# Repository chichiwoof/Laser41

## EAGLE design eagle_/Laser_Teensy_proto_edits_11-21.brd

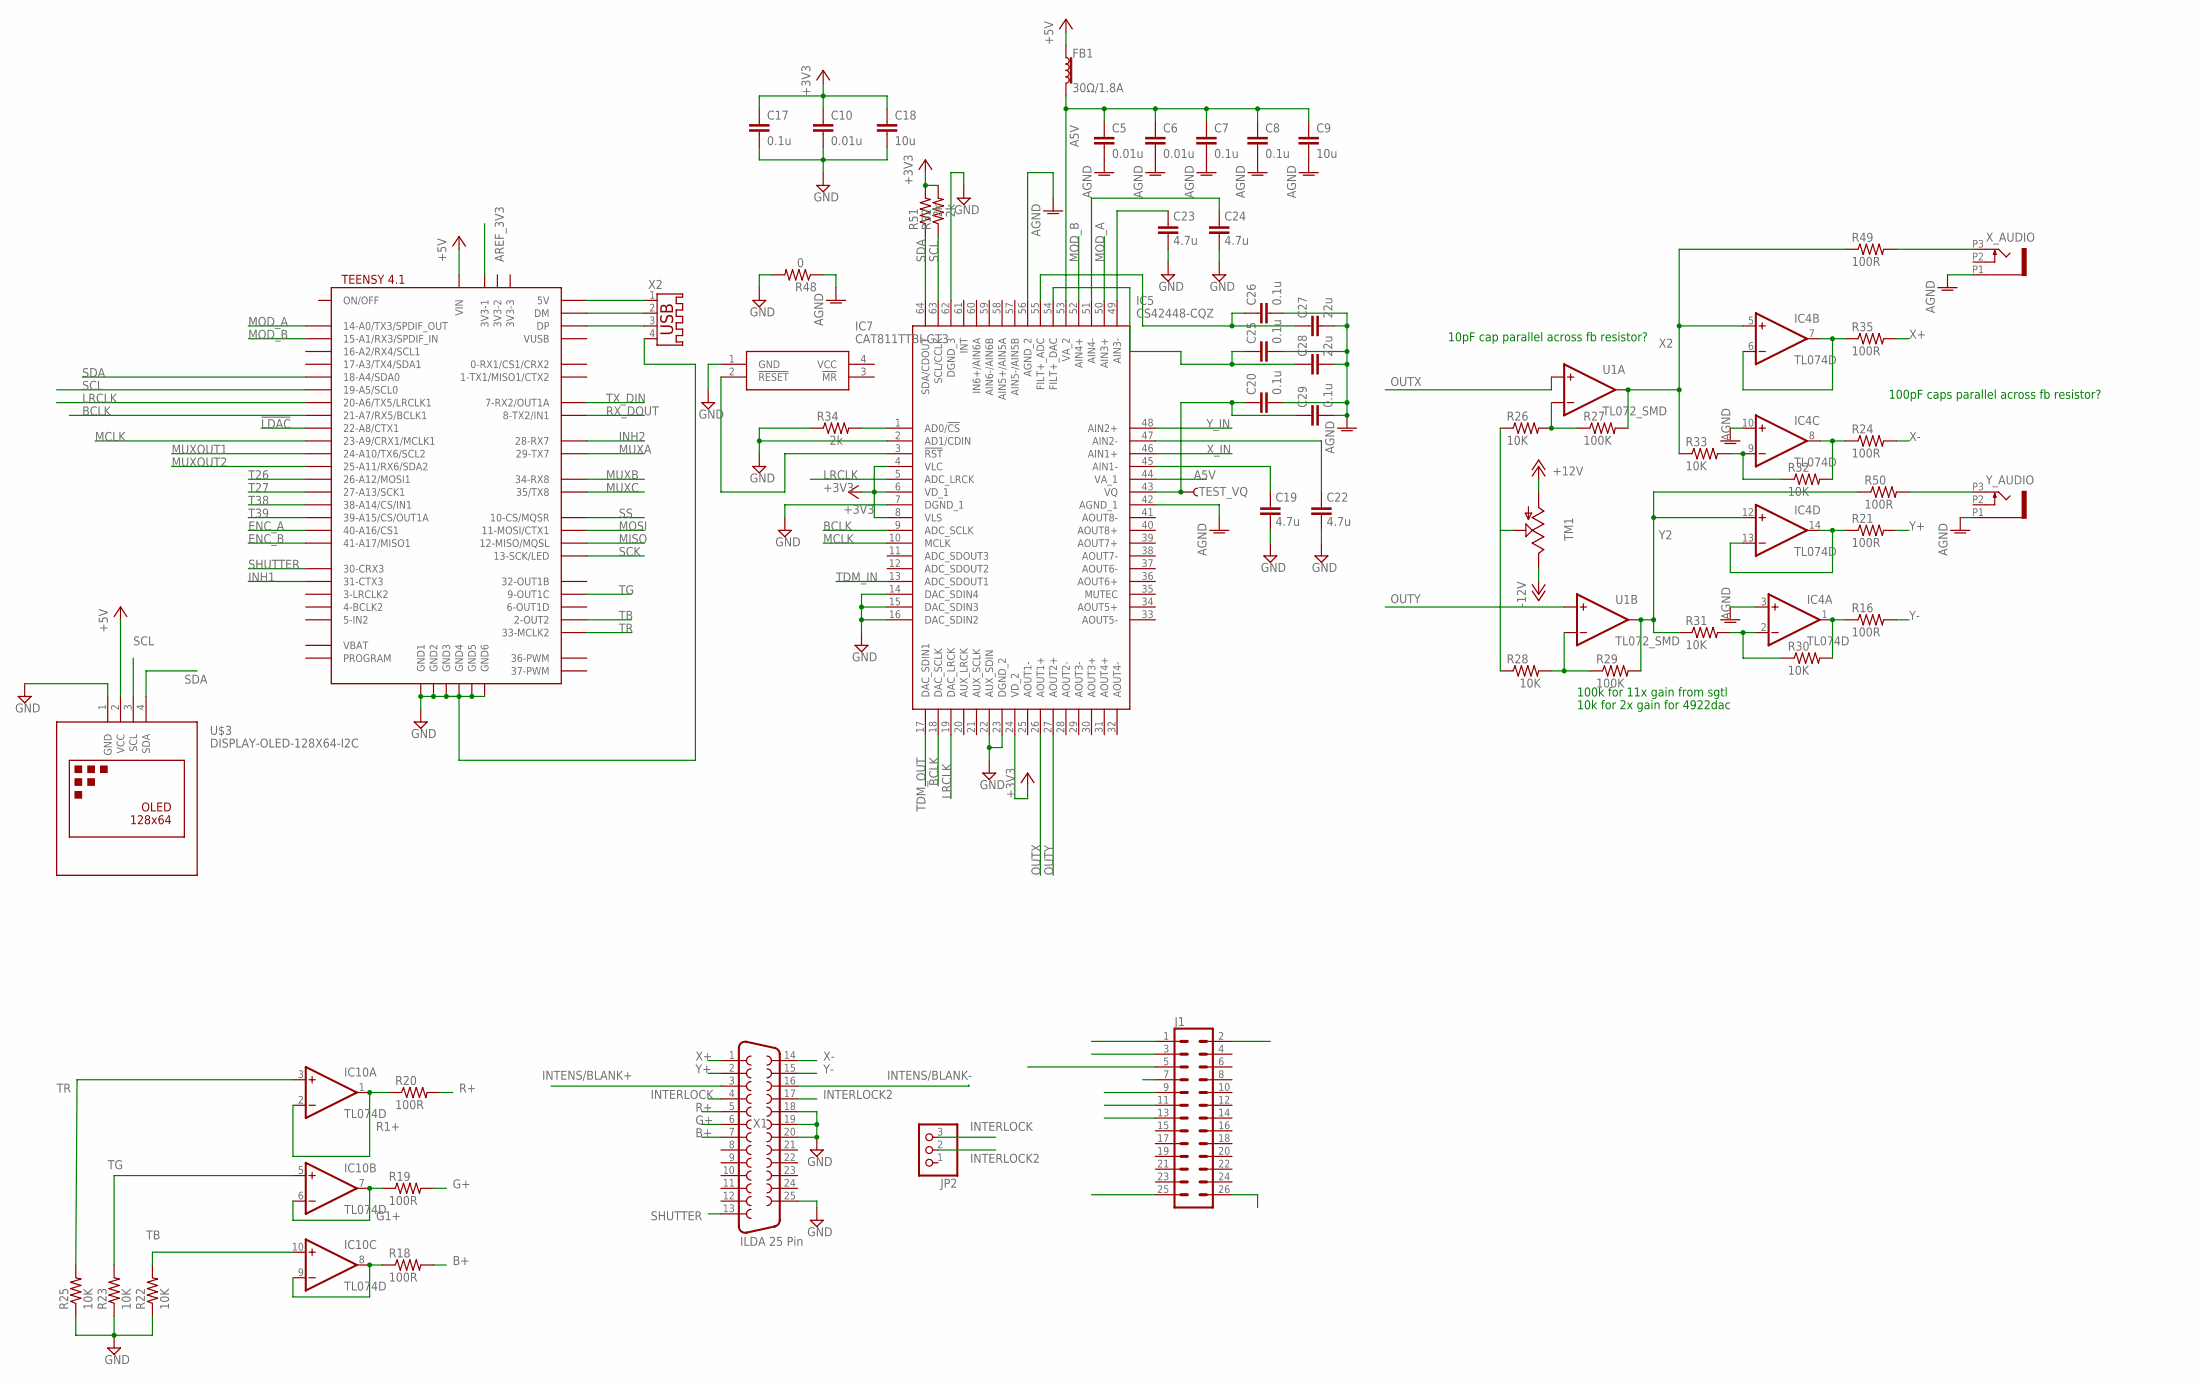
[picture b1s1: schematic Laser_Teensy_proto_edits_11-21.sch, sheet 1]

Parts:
C5, C6, C10: 0.01u; C0603
C7, C8, C17, C20, C25, C26, C29: 0.1u; C0603
C9, C18: 10u; C0603
C19, C22, C23, C24: 4.7u; C0603
C27, C28: 22u; C0603
FB1: 30Ω/1.8A; 0603
IC4, IC10: TL074D; SO14
IC5: CS42448-CQZ; QFP50P1200X1200X160-64N
IC7: CAT811TTBI-GT3; 4-PIN-SOT-143(BI-SUFFIX-CASE-5
J1: CONN_13X22X13; 2X13
JP2: PINHD-1X3; 1X03
R16, R18, R19, R20, R21, R24, R35, R49, R50: 100R; R0603
R22, R23, R25, R26, R28, R30, R31, R32, R33: 10K; R0603
R27, R29: 100K; R0603
R34, R51, R52: 2k; R0603
R48: 0; R0603
TEST_VQ: TEST-VQ; PAD.03X.03
TM1: TRIM; 6MM
U1: TL072_SMD; SO08
U$2: TEENSY41-E; TENNSY41-E
U$3: DISPLAY-OLED-128X64-I2C
X1: ILDA 25 Pin; F25D
X2: USB-A003
X_AUDIO: PJ301_THONKICONN6; WQP_PJ_301M6
Y_AUDIO: PJ301_THONKICONN6; WQP_PJ_301M6

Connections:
!LDAC: U$2.22-A8/CTX1
+3V3: C10.1, C17.1, C18.1, IC5.4 (VLC), IC5.6 (VD_1), IC5.8 (VLS), IC5.24 (VD_2), R51.2, R52.2; also elsewhere on the board
+5V: FB1.1, U$2.VIN, U$3.2 (VCC); also elsewhere on the board
+12V: TM1.A; also elsewhere on the board
-12V: TM1.E; also elsewhere on the board
A5V: C5.1, C6.1, C7.1, C8.1, C9.1, FB1.2, IC5.44 (VA_1), IC5.53 (VA_2)
AGND: C5.2, C6.2, C7.2, C8.2, C9.2, C20.2, C25.2, C26.2, C27.2, C28.2, C29.2, IC4.3 (+IN), IC4.10 (+IN), IC5.42 (AGND_1), IC5.56 (AGND_2), R48.1, X_AUDIO.P1 (1), Y_AUDIO.P1 (1); also elsewhere on the board
AREF_3V3: U$2.3V3-1
B1+1: IC10.8 (OUT), IC10.9 (-IN), R18.1
B+: R18.2, X1.7
BCLK: IC5.9 (ADC_SCLK), IC5.18 (DAC_SCLK), U$2.21-A7/RX5/BCLK1
ENC_A: U$2.40-A16/CS1; also elsewhere on the board
ENC_B: U$2.41-A17/MISO1; also elsewhere on the board
G1+: IC10.6 (-IN), IC10.7 (OUT), R19.1
G+: R19.2, X1.6
GND: C10.2, C17.2, C18.2, C19.2, C22.2, C23.2, C24.2, IC5.2 (AD1/CDIN), IC5.7 (DGND_1), IC5.14 (DAC_SDIN4), IC5.15 (DAC_SDIN3), IC5.16 (DAC_SDIN2), IC5.22 (AUX_SDIN), IC5.23 (DGND_2), IC5.62 (DGND_3), IC7.1 (GND), R22.1, R23.1, R25.1, R34.1, R48.2, U$2.GND1, U$2.GND2, U$2.GND3, U$2.GND4, U$2.GND5, U$2.GND6, U$3.1 (GND), X1.18, X1.19, X1.20, X1.25, X2.4; also elsewhere on the board
INH1: U$2.31-CTX3; also elsewhere on the board
INH2: U$2.28-RX7; also elsewhere on the board
INTENS/BLANK+: X1.3
INTENS/BLANK-: X1.16
INTERLOCK: JP2.3, X1.4
INTERLOCK2: JP2.2, X1.17
LRCLK: IC5.5 (ADC_LRCK), IC5.19 (DAC_LRCK), U$2.20-A6/TX5/LRCLK1
MCLK: IC5.10 (MCLK), U$2.23-A9/CRX1/MCLK1
MISO: U$2.12-MISO/MQSL
MOD_A: IC5.50 (AIN3+), U$2.14-A0/TX3/SPDIF_OUT; also elsewhere on the board
MOD_B: IC5.52 (AIN4+), U$2.15-A1/RX3/SPDIF_IN; also elsewhere on the board
MOSI: U$2.11-MOSI/CTX1
MUXA: U$2.29-TX7; also elsewhere on the board
MUXB: U$2.34-RX8; also elsewhere on the board
MUXC: U$2.35-TX8 (35/TX8); also elsewhere on the board
MUXOUT1: U$2.24-A10/TX6/SCL2; also elsewhere on the board
MUXOUT2: U$2.25-A11/RX6/SDA2; also elsewhere on the board
unnamed: IC5.3 (!RST), IC7.2 (!RESET)
unnamed: R26.1, R28.1, TM1.S
unnamed: U$2.+5V (5V), X2.1
unnamed: U$2.DM, X2.2
unnamed: U$2.DP, X2.3
unnamed: R49.2, X_AUDIO.P3 (3)
unnamed: C23.1, IC5.49 (AIN3-)
unnamed: R50.2, Y_AUDIO.P3 (3)
unnamed: R26.2, R27.1, U1.2 (-IN)
unnamed: R28.2, R29.1, U1.6 (-IN)
unnamed: IC4.9 (-IN), R32.1, R33.2
unnamed: IC4.2 (-IN), R30.1, R31.2
unnamed: C24.1, IC5.51 (AIN4-)
unnamed: C19.1, IC5.45 (AIN1-)
unnamed: C22.1, IC5.47 (AIN2-)
unnamed: IC5.1 (AD0/!CS), R34.2
unnamed: C26.1, C27.1, IC5.55 (FILT+_ADC)
unnamed: C25.1, C28.1, IC5.54 (FILT+_DAC)
unnamed: C20.1, C29.1, IC5.43 (VQ), TEST_VQ.P$1
OUTX: IC5.26 (AOUT1+), U1.3 (+IN)
OUTY: IC5.27 (AOUT2+), U1.5 (+IN)
R1+: IC10.1 (OUT), IC10.2 (-IN), R20.1
R+: R20.2, X1.5
RX_DOUT: U$2.8-TX2/IN1
SCK: U$2.13-SCK/LED
SCL: IC5.63 (SCL/CCLK), R52.1, U$2.19-A5/SCL0, U$3.3 (SCL)
SDA: IC5.64 (SDA/CDOUT), R51.1, U$2.18-A4/SDA0, U$3.4 (SDA)
SHUTTER: U$2.30-CRX3, X1.13
SS: U$2.10-CS\MQSR (10-CS/MQSR)
T26: U$2.26-A12/MOSI1; also elsewhere on the board
T27: U$2.27-A13/SCK1; also elsewhere on the board
T38: U$2.38-A14/CS/IN1; also elsewhere on the board
T39: U$2.39-A15/CS/OUT1A
TB: IC10.10 (+IN), R22.2, U$2.2-OUT2
TDM_IN: IC5.13 (ADC_SDOUT1)
TDM_OUT: IC5.17 (DAC_SDIN1)
TG: IC10.5 (+IN), R23.2, U$2.9-OUT1C
TR: IC10.3 (+IN), R25.2, U$2.33-MCLK2
TX_DIN: U$2.7-RX2/OUT1A
VCC: IC7.4 (VCC)
X1+: IC4.6 (-IN), IC4.7 (OUT), R35.1
X1-: IC4.8 (OUT), R24.1, R32.2
X2: IC4.5 (+IN), R27.2, R33.1, R49.1, U1.1 (OUT)
X+: R35.2, X1.1
X-: R24.2, X1.14
X_IN: IC5.46 (AIN1+); also elsewhere on the board
Y1+: IC4.13 (-IN), IC4.14 (OUT), R21.1
Y1-: IC4.1 (OUT), R16.1, R30.2
Y2: IC4.12 (+IN), R29.2, R31.1, R50.1, U1.7 (OUT)
Y+: R21.2, X1.2
Y-: R16.2, X1.15
Y_IN: IC5.48 (AIN2+); also elsewhere on the board

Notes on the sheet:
10pF cap parallel across fb resistor?
100pF caps parallel across fb resistor?
100k for 11x gain from sgtl
10k for 2x gain for 4922dac

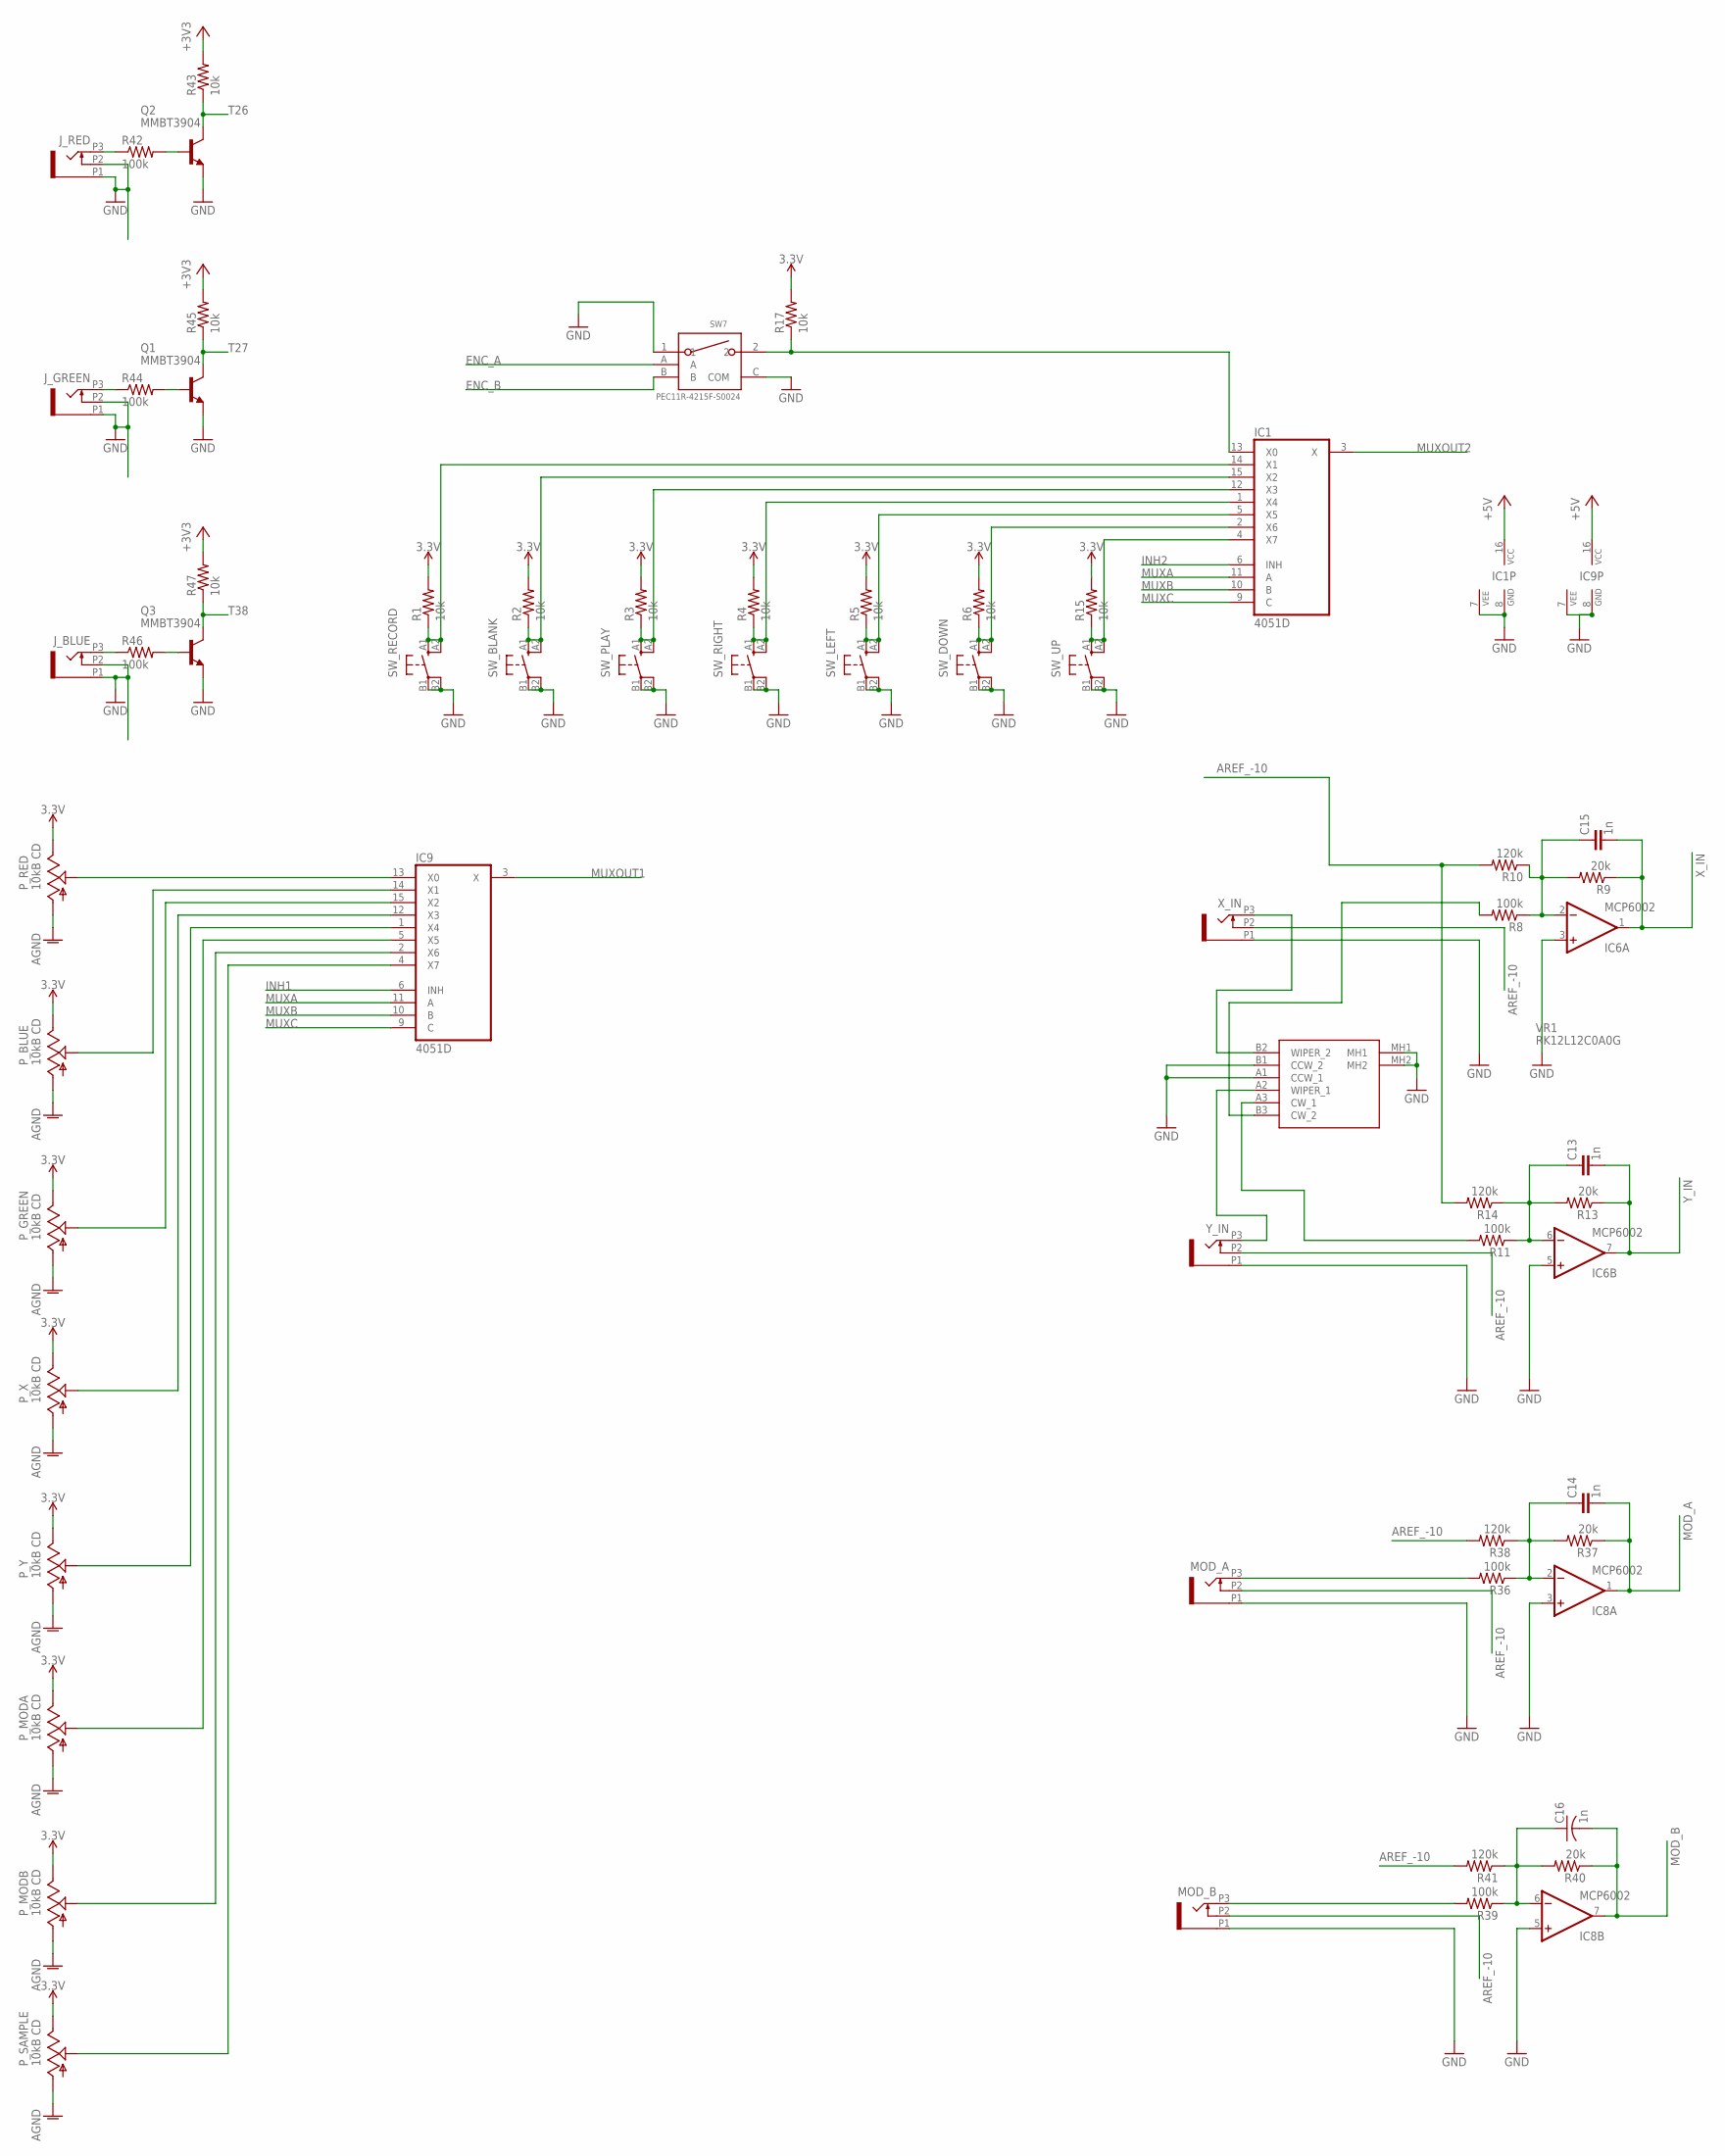
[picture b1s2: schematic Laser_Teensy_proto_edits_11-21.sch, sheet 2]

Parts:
C13, C14, C15: 1n; C0603
C16: 1n; C0603K
IC1, IC9: 4051D; SO16
IC6, IC8: MCP6002; SO08
J_BLUE: PJ301_THONKICONN6; WQP_PJ_301M6
J_GREEN: PJ301_THONKICONN6; WQP_PJ_301M6
J_RED: PJ301_THONKICONN6; WQP_PJ_301M6
MOD_A: PJ301_THONKICONN6; WQP_PJ_301M6
MOD_B: PJ301_THONKICONN6; WQP_PJ_301M6
P_BLUE: 10kB CD; ALPS_POT_VERTICAL_PS
P_GREEN: 10kB CD; ALPS_POT_VERTICAL_PS
P_MODA: 10kB CD; ALPS_POT_VERTICAL_PS
P_MODB: 10kB CD; ALPS_POT_VERTICAL_PS
P_RED: 10kB CD; ALPS_POT_VERTICAL_PS
P_SAMPLE: 10kB CD; ALPS_POT_VERTICAL_PS
P_X: 10kB CD; ALPS_POT_VERTICAL_PS
P_Y: 10kB CD; ALPS_POT_VERTICAL_PS
Q1, Q2, Q3: MMBT3904; SOT23-BEC
R1, R2, R3, R4, R5, R6, R15, R17, R43, R45, R47: 10k; R0603
R8, R11, R36, R39, R42, R44, R46: 100k; R0603
R9, R13, R37, R40: 20k; R0603
R10, R14, R38, R41: 120k; R0603
SW7: PEC11R-4215F-S0024
SW_BLANK: D6R
SW_DOWN: D6R
SW_LEFT: D6R
SW_PLAY: D6R
SW_RECORD: D6R
SW_RIGHT: D6R
SW_UP: D6R
VR1: RK12L12C0A0G
X_IN: PJ301_THONKICONN6; WQP_PJ_301M6
Y_IN: PJ301_THONKICONN6; WQP_PJ_301M6

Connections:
3.3V: P_BLUE.P$1 (E), P_GREEN.P$1 (E), P_MODA.P$1 (E), P_MODB.P$1 (E), P_RED.P$1 (E), P_SAMPLE.P$1 (E), P_X.P$1 (E), P_Y.P$1 (E), R1.2, R2.2, R3.2, R4.2, R5.2, R6.2, R15.2, R17.2
+3V3: R43.2, R45.2, R47.2; also elsewhere on the board
+5V: IC1.16 (VCC), IC9.16 (VCC); also elsewhere on the board
AGND: P_BLUE.P$3 (A), P_GREEN.P$3 (A), P_MODA.P$3 (A), P_MODB.P$3 (A), P_RED.P$3 (A), P_SAMPLE.P$3 (A), P_X.P$3 (A), P_Y.P$3 (A); also elsewhere on the board
AREF_-10: MOD_A.P2 (2), MOD_B.P2 (2), R10.2, R14.2, R38.2, R41.2, X_IN.P2 (2), Y_IN.P2 (2); also elsewhere on the board
ENC_A: SW7.A; also elsewhere on the board
ENC_B: SW7.B; also elsewhere on the board
GND: IC1.7 (VEE), IC1.8 (GND), IC6.3 (+IN), IC6.5 (+IN), IC8.3 (+IN), IC8.5 (+IN), IC9.7 (VEE), IC9.8 (GND), J_BLUE.P1 (1), J_BLUE.P2 (2), J_GREEN.P1 (1), J_GREEN.P2 (2), J_RED.P1 (1), J_RED.P2 (2), MOD_A.P1 (1), MOD_B.P1 (1), Q1.E, Q2.E, Q3.E, SW7.1, SW7.C (COM), SW_BLANK.B1, SW_BLANK.B2 (P1), SW_DOWN.B1, SW_DOWN.B2 (P1), SW_LEFT.B1, SW_LEFT.B2 (P1), SW_PLAY.B1, SW_PLAY.B2 (P1), SW_RECORD.B1, SW_RECORD.B2 (P1), SW_RIGHT.B1, SW_RIGHT.B2 (P1), SW_UP.B1, SW_UP.B2 (P1), VR1.A1 (CCW_1), VR1.B1 (CCW_2), VR1.MH1, VR1.MH2, X_IN.P1 (1), Y_IN.P1 (1); also elsewhere on the board
INH1: IC9.6 (INH); also elsewhere on the board
INH2: IC1.6 (INH); also elsewhere on the board
MOD_A: C14.2, IC8.1 (OUT), R37.1; also elsewhere on the board
MOD_B: C16.2, IC8.7 (OUT), R40.1; also elsewhere on the board
MUXA: IC1.11 (A), IC9.11 (A); also elsewhere on the board
MUXB: IC1.10 (B), IC9.10 (B); also elsewhere on the board
MUXC: IC1.9 (C), IC9.9 (C); also elsewhere on the board
MUXOUT1: IC9.3 (X); also elsewhere on the board
MUXOUT2: IC1.3 (X); also elsewhere on the board
unnamed: C15.1, IC6.2 (-IN), R8.1, R9.2, R10.1
unnamed: VR1.B2 (WIPER_2), X_IN.P3 (3)
unnamed: C13.1, IC6.6 (-IN), R11.1, R13.2, R14.1
unnamed: C14.1, IC8.2 (-IN), R36.1, R37.2, R38.1
unnamed: R8.2, VR1.B3 (CW_2)
unnamed: IC1.14 (X1), R1.1, SW_RECORD.A1 (S), SW_RECORD.A2 (S1)
unnamed: IC1.15 (X2), R2.1, SW_BLANK.A1 (S), SW_BLANK.A2 (S1)
unnamed: IC1.12 (X3), R3.1, SW_PLAY.A1 (S), SW_PLAY.A2 (S1)
unnamed: IC9.13 (X0), P_RED.P$2 (S)
unnamed: IC1.1 (X4), R4.1, SW_RIGHT.A1 (S), SW_RIGHT.A2 (S1)
unnamed: IC9.14 (X1), P_BLUE.P$2 (S)
unnamed: VR1.A2 (WIPER_1), Y_IN.P3 (3)
unnamed: IC1.5 (X5), R5.1, SW_LEFT.A1 (S), SW_LEFT.A2 (S1)
unnamed: IC9.15 (X2), P_GREEN.P$2 (S)
unnamed: IC1.2 (X6), R6.1, SW_DOWN.A1 (S), SW_DOWN.A2 (S1)
unnamed: IC9.12 (X3), P_X.P$2 (S)
unnamed: IC9.1 (X4), P_Y.P$2 (S)
unnamed: IC1.4 (X7), R15.1, SW_UP.A1 (S), SW_UP.A2 (S1)
unnamed: C16.1, IC8.6 (-IN), R39.1, R40.2, R41.1
unnamed: IC1.13 (X0), R17.1, SW7.2
unnamed: IC9.5 (X5), P_MODA.P$2 (S)
unnamed: IC9.2 (X6), P_MODB.P$2 (S)
unnamed: IC9.4 (X7), P_SAMPLE.P$2 (S)
unnamed: R11.2, VR1.A3 (CW_1)
unnamed: J_RED.P3 (3), R42.1
unnamed: MOD_A.P3 (3), R36.2
unnamed: MOD_B.P3 (3), R39.2
unnamed: Q1.B, R44.2
unnamed: J_GREEN.P3 (3), R44.1
unnamed: Q3.B, R46.2
unnamed: J_BLUE.P3 (3), R46.1
unnamed: Q2.B, R42.2
T26: Q2.C, R43.1; also elsewhere on the board
T27: Q1.C, R45.1; also elsewhere on the board
T38: Q3.C, R47.1; also elsewhere on the board
X_IN: C15.2, IC6.1 (OUT), R9.1; also elsewhere on the board
Y_IN: C13.2, IC6.7 (OUT), R13.1; also elsewhere on the board

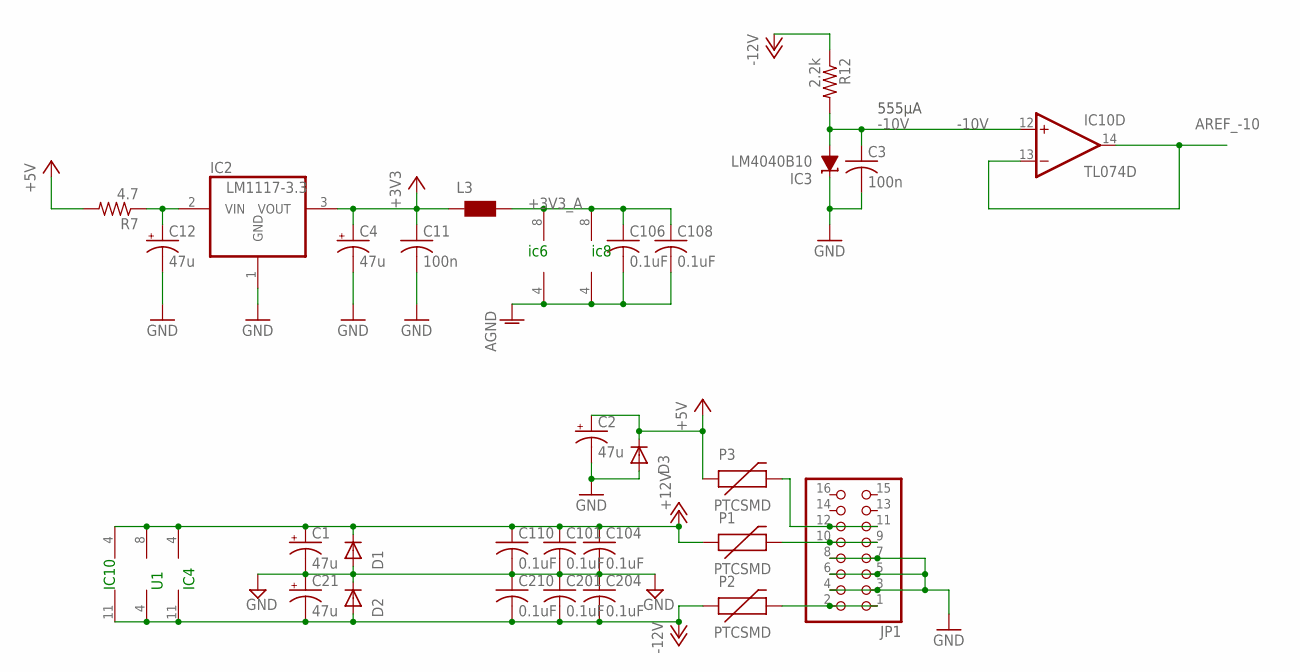
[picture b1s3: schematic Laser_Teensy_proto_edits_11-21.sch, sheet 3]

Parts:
C1, C2, C4, C12, C21: 47u; E3,5-8
C3, C11: 100n; C0603
C101, C104, C106, C108, C110, C201, C204, C210: 0.1uF; C0603
D1, D2, D3: 1N5819HW; SOD123
IC2: LM1117-3.3; TO252
IC3: LM4040B10; DBZ_R-PDSO-G3
IC4, IC10: TL074D; SO14
IC6, IC8: MCP6002; SO08
JP1: PINHD-2X8; 2X08
L3: WE-CBF_0603; 0603
P1, P2, P3: PTCSMD; PTC-1206
R7: 4.7; R0603
R12: 2.2k; R0603
U1: TL072_SMD; SO08

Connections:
+3V3: C4.+, C11.1, IC2.3 (VOUT), L3.1; also elsewhere on the board
+3V3_A: C106.1, C108.1, IC6.8 (V+), IC8.8 (V+), L3.2
+5V: C2.+, D3.C, P3.1, R7.2; also elsewhere on the board
+12V: C1.+, C101.1, C104.1, C110.1, D1.C, IC4.4 (V+), IC10.4 (V+), P1.1, U1.8 (V+); also elsewhere on the board
-10V: C3.1, IC3.2 (A), IC10.12 (+IN), R12.2
-12V: C21.-, C201.2, C204.2, C210.2, D2.A, IC4.11 (V-), IC10.11 (V-), P2.1, R12.1, U1.4 (V-); also elsewhere on the board
AGND: C106.2, C108.2, IC6.4 (V-), IC8.4 (V-); also elsewhere on the board
AREF_-10: IC10.13 (-IN), IC10.14 (OUT); also elsewhere on the board
GND: C1.-, C2.-, C3.2, C4.-, C11.2, C12.-, C21.+, C101.2, C104.2, C110.2, C201.1, C204.1, C210.1, D1.A, D2.C, D3.A, IC2.1 (GND), IC3.1 (C), JP1.3, JP1.4, JP1.5, JP1.6, JP1.7, JP1.8; also elsewhere on the board
unnamed: JP1.1, JP1.2, P2.2
unnamed: JP1.9, JP1.10, P1.2
unnamed: JP1.11, JP1.12, P3.2
unnamed: C12.+, IC2.2 (VIN), R7.1

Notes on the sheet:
555µA
IC4
IC10
ic6
ic8

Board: 2 copper layers, 146 parts (77 on the bottom side), 111 nets, no tracks yet.

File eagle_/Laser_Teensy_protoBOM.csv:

"Qty";"Value";"Device";"Package";"Parts";"Description";"ARROW_PART_NUMBER";"ARROW_PRICE-STOCK";"CREATED_BY";"DESCRIPTION";"DIGIKEY_PART_NUMBER";"HEIGHT";"MANUFACTURER";"MANUFACTURER_NAME";"MANUFACTURER_PART_NUMBER";"MF";"MOUSER_PART_NUMBER";"MOUSER_PRICE-STOCK";"MPN";"OC_FARNELL";"OC_NEWARK";"POPULARITY";"SPICEPREFIX";
"1";"";"CONN_02";"1X02";"J2";"Multi connection point. Often used as Generic Header-pin footprint for 0.1 inch spaced/style header connections";"";"";"";"";"";"";"";"";"";"";"";"";"";"";"";"";"";
"1";"";"CONN_05";"1X05";"J1";"Multi connection point. Often used as Generic Header-pin footprint for 0.1 inch spaced/style header connections";"";"";"";"";"";"";"";"";"";"";"";"";"";"";"";"";"";
"2";"";"PINHD-1X2";"1X02";"JP4, JP5";"PIN HEADER";"";"";"";"";"";"";"";"";"";"";"";"";"";"";"";"98";"";
"1";"";"PINHD-1X3";"1X03";"JP2";"PIN HEADER";"";"";"";"";"";"";"";"";"";"";"";"";"";"";"";"92";"";
"1";"";"PINHD-2X8";"2X08";"JP1";"PIN HEADER";"";"";"";"";"";"";"";"";"";"";"";"";"";"";"";"6";"";
"1";"";"USB-A003";"USB-A003";"X2";"USB connector";"";"";"";"";"";"";"";"";"";"";"";"";"";"unknown";"unknown";"1";"";
"1";"";"WE-CBF_0603";"0603";"L3";"SMD EMI Suppression Ferrite Beads";"";"";"";"";"";"";"";"";"";"";"";"";"";"";"";"";"";
"9";"0.1uF";"C-USC0603";"C0603";"C20, C101, C104, C106, C108, C110, C201, C204, C210";"CAPACITOR, American symbol";"";"";"";"";"";"";"";"";"";"";"";"";"";"";"";"";"";
"2";"100K";"R-US_0204/5";"0204/5";"R27, R29";"RESISTOR, American symbol";"";"";"";"";"";"";"";"";"";"";"";"";"";"";"";"18";"R";
"7";"100R";"R-US_0204/5";"0204/5";"R16, R18, R19, R20, R21, R24, R35";"RESISTOR, American symbol";"";"";"";"";"";"";"";"";"";"";"";"";"";"";"";"18";"R";
"7";"100k";"R-US_0204/5";"0204/5";"R8, R11, R36, R39, R42, R44, R46";"RESISTOR, American symbol";"";"";"";"";"";"";"";"";"";"";"";"";"";"";"";"18";"R";
"2";"100n";"C-USC0603";"C0603";"C3, C11";"CAPACITOR, American symbol";"";"";"";"";"";"";"";"";"";"";"";"";"";"";"";"";"";
"8";"10K";"R-US_0204/5";"0204/5";"R22, R23, R25, R26, R28, R30, R31, R33";"RESISTOR, American symbol";"";"";"";"";"";"";"";"";"";"";"";"";"";"";"";"18";"R";
"1";"10K";"R-US_R0603";"R0603";"R32";"RESISTOR, American symbol";"";"";"";"";"";"";"";"";"";"";"";"";"";"";"";"";"";
"3";"10k";"R-US_0204/5";"0204/5";"R43, R45, R47";"RESISTOR, American symbol";"";"";"";"";"";"";"";"";"";"";"";"";"";"";"";"18";"R";
"8";"10kB CD";"POT_USVERTICAL_PS";"ALPS_POT_VERTICAL_PS";"P_BLUE, P_GREEN, P_MODA, P_MODB, P_RED, P_SAMPLE, P_X, P_Y";"";"";"";"";"";"";"";"";"";"";"";"";"";"";"";"";"";"";
"4";"120k";"R-US_0204/5";"0204/5";"R10, R14, R38, R41";"RESISTOR, American symbol";"";"";"";"";"";"";"";"";"";"";"";"";"";"";"";"18";"R";
"3";"1N5819HW";"DIODE-SOD123";"SOD123";"D1, D2, D3";"DIODE";"";"";"";"";"";"";"";"";"";"";"";"";"";"";"";"";"";
"4";"1n";"C-US050-025X075";"C050-025X075";"C13, C14, C15, C16";"CAPACITOR, American symbol";"";"";"";"";"";"";"";"";"";"";"";"";"";"";"";"0";"C";
"1";"2.2k";"R-US_0204/5";"0204/5";"R12";"RESISTOR, American symbol";"";"";"";"";"";"";"";"";"";"";"";"";"";"";"";"18";"R";
"4";"20k";"R-US_0204/5";"0204/5";"R9, R13, R37, R40";"RESISTOR, American symbol";"";"";"";"";"";"";"";"";"";"";"";"";"";"";"";"18";"R";
"1";"4.7";"R-US_R1206";"R1206";"R7";"RESISTOR, American symbol";"";"";"";"";"";"";"";"";"";"";"";"";"";"";"";"";"";
"2";"4051D";"4051D";"SO16";"IC1, IC9";"8-channel ANALOG MULTIPLEXER";"";"";"";"";"";"";"";"";"";"";"";"";"";"";"";"5";"";
"5";"47u";"CPOL-USE3.5-8";"E3,5-8";"C1, C2, C4, C12, C21";"POLARIZED CAPACITOR, American symbol";"";"";"";"";"";"";"";"";"";"";"";"";"";"";"";"9";"C";
"7";"D6R";"D6R";"D6R";"SW_BLANK, SW_DOWN, SW_LEFT, SW_PLAY, SW_RECORD, SW_RIGHT, SW_UP";"C&K D6R";"";"";"";"";"";"";"";"";"";"";"";"";"";"";"";"";"";
"1";"DISPLAY-OLED-128X64-I2C";"DISPLAY-OLED-128X64-I2C";"DISPLAY-OLED-128X64-I2C";"U$3";"128x64 Dot Matrix OLED Module based on SSD1306 chip";"";"";"";"";"";"";"";"";"";"";"";"";"";"";"";"";"";
"1";"ILDA 25 Pin";"F25D";"F25D";"X1";"D-SUB 25";"";"";"";"";"";"";"";"";"";"";"";"";"";"";"";"";"";
"1";"LM1117-3.3";"REG1117T";"TO252";"IC2";"800mA and 1A Low Dropout (LDO) Positive Regulator";"";"";"";"";"";"";"";"";"";"";"";"";"";"";"";"";"";
"1";"LM4040B10";"LM4041B12DBZ";"DBZ_R-PDSO-G3";"IC3";"PRECISION MICROPOWER SHUNT VOLTAGE REFERENCE";"";"";"";"";"";"";"";"";"";"";"";"";"";"";"";"";"";
"1";"MCP4922-E_ST";"MCP4922-E_ST";"SOP65P638X110-14N";"IC7";"Microchip MCP4922-E/ST, 2-channel 12 bit Serial DAC, 14-Pin TSSOP";"MCP4922-E/ST";"https://www.arrow.com/en/products/mcp4922-est/microchip-technology";"";"Microchip MCP4922-E/ST, 2-channel 12 bit Serial DAC, 14-Pin TSSOP";"";"1.1mm";"";"Microchip";"MCP4922-E/ST";"";"579-MCP4922-E/ST";"https://www.mouser.co.uk/ProductDetail/Microchip-Technology/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";"";"";"";"";"";
"2";"MCP6002";"TL072D";"SO08";"IC6, IC8";"OP AMP";"";"";"";"";"";"";"";"";"";"";"";"";"";"";"";"";"";
"3";"MMBT3904";"MMBT3904LT1-NPN-SOT23-BEC";"SOT23-BEC";"Q1, Q2, Q3";"NPN Transistror";"";"";"";"";"";"";"";"";"";"";"";"";"";"";"";"";"";
"1";"PEC11R-4215F-S0024";"PEC11R-4215F-S0024";"PEC11R-4215F-S0024";"SW7";"ROTARY ENCODER MECHANICAL 24PPR";"";"";"PCBLayout.com";"";"PEC11R-4215F-S0024-ND";"";"Bourns Inc.";"";"";"";"";"";"PEC11R-4215F-S0024";"";"";"";"";
"7";"PJ301_THONKICONN6";"PJ301_THONKICONN6";"WQP_PJ_301M6";"J_BLUE, J_GREEN, J_RED, MOD_A, MOD_B, X_IN, Y_IN";"";"";"";"";"";"";"";"";"";"";"";"";"";"";"";"";"";"";
"3";"PTCSMD";"PTCSMD";"PTC-1206";"P1, P2, P3";"Resettable Fuse PTC";"";"";"";"";"";"";"";"";"";"";"";"";"";"";"";"";"";
"1";"RK12L12C0A0G";"RK12L12C0A0G";"RK12L12C0A0G";"VR1";"Alps Potentiometer RK12L Series with a 6 mm Dia. Shaft 10k +/-20%, Logarithmic, Through Hole";"";"";"";"Alps Potentiometer RK12L Series with a 6 mm Dia. Shaft 10k +/-20%, Logarithmic, Through Hole";"";"15mm";"";"ALPS";"RK12L12C0A0G";"";"688-RK12L12C0A0G";"https://www.mouser.co.uk/ProductDetail/ALPS/RK12L12C0A0G?qs=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";"";"";"";"";"";
"1";"TEENSY41-E";"TEENSY41-E";"TENNSY41-E";"U$2";"";"";"";"";"";"";"";"";"";"";"";"";"";"";"";"";"";"";
"1";"TL072_SMD";"TL072_SMD";"SO08";"U1";"Generic Dual Op Amp";"";"";"";"";"";"";"";"";"";"";"";"";"";"";"";"";"";
"2";"TL074D";"TL074D";"SO14";"IC4, IC10";"OP AMP";"";"";"";"";"";"";"";"";"";"";"";"";"";"";"";"0";"";

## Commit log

2021-06-03 first laser41 commit
2021-06-03 add eagle
2021-06-07 sample knob fixed, need to map
2021-06-08 analog button mux and encoder beginnings
2021-06-08 added encoder and fileName
2021-06-08 added pwm colors etc
2021-06-09 final project tues
2021-11-25 pcb fixes and CS42448
2022-02-24 first commit PAT from mac

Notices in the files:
parts and their libraries:
diy-modules: Released under the Creative Commons Attribution 4.0 International License: http://creativecommons.org/licenses/by/4.0
SparkFun-Coils: Licensing: Creative Commons ShareAlike 4.0 International - https://creativecommons.org/licenses/by-sa/4.0
